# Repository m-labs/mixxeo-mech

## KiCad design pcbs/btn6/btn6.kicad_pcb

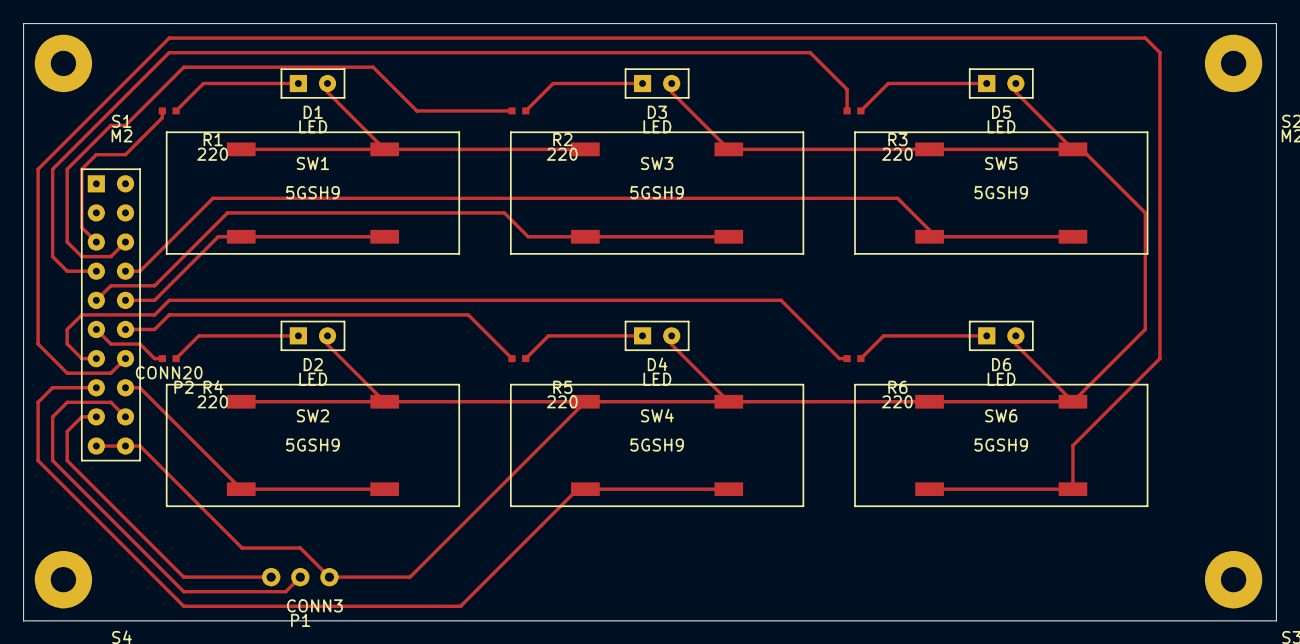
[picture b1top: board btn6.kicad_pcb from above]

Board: 2 copper layers, 109.2 x 52.1 mm, 24 parts (0 on the bottom side), 21 nets.

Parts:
D1, D2, D3, D4, D5, D6: LED; LED5x2
P1: CONN3
P2: CONN20
R1, R2, R3, R4, R5, R6: 220; 0402
S1, S2, S3, S4: M2
SW1, SW2, SW3, SW4, SW5, SW6: 5GSH9

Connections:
unnamed: P2.12, R5.1
unnamed: P2.13, R6.1
unnamed: P2.14, SW6.3, SW6.4
unnamed: P1.1, P2.17
unnamed: P1.2, P2.18
unnamed: P2.8, SW5.3, SW5.4
unnamed: P2.10, SW1.3, SW1.4
unnamed: D5.1, R3.2
unnamed: D3.1, R2.2
unnamed: P2.5, R1.1
unnamed: P2.16, SW2.3, SW2.4
unnamed: P2.15, SW4.3, SW4.4
unnamed: P2.9, SW3.3, SW3.4
unnamed: P2.6, R2.1
unnamed: P2.7, R3.1
unnamed: P2.11, R4.1
unnamed: D1.1, R1.2
unnamed: D6.1, R6.2
unnamed: D4.1, R5.2
unnamed: D2.1, R4.2
unnamed: D1.2, D2.2, D3.2, D4.2, D5.2, D6.2, P1.3, P2.19, P2.20, SW1.1, SW1.2, SW2.1, SW2.2, SW3.1, SW3.2, SW4.1, SW4.2, SW5.1, SW5.2, SW6.1, SW6.2

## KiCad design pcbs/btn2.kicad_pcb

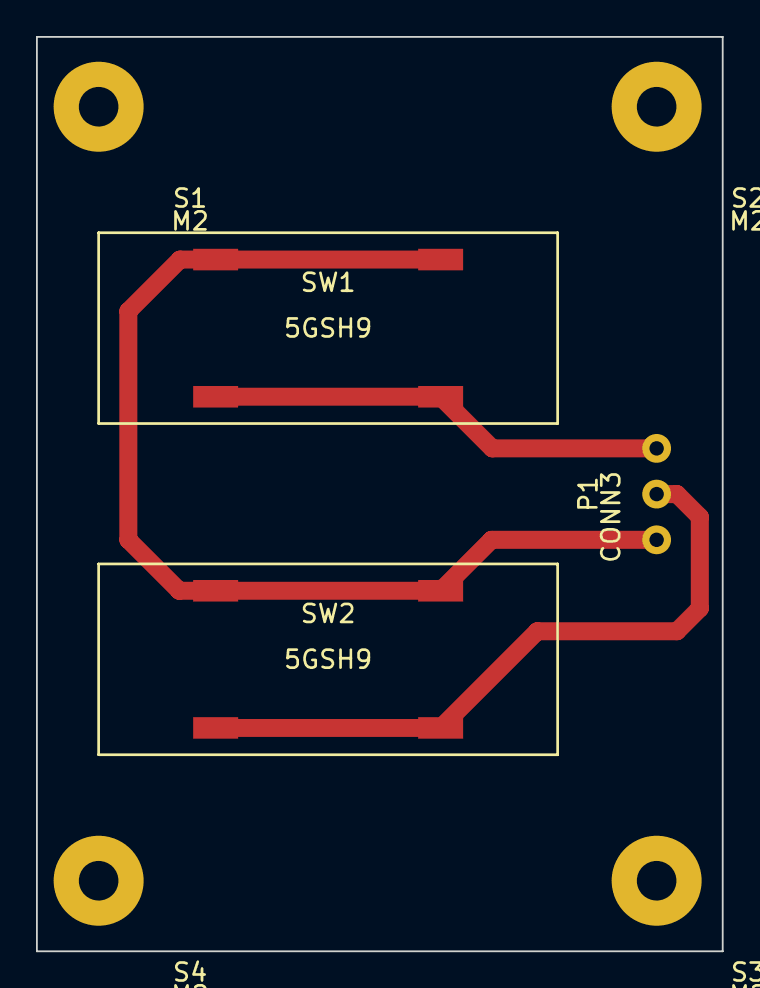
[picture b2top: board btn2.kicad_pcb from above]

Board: 2 copper layers, 38.1 x 50.8 mm, 7 parts (0 on the bottom side), 3 nets.

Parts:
P1: CONN3
S1, S2, S3, S4: M2
SW1, SW2: 5GSH9

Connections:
unnamed: P1.1, SW1.3, SW1.4
unnamed: P1.2, SW2.3, SW2.4
unnamed: P1.3, SW1.1, SW1.2, SW2.1, SW2.2

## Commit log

2014-04-23 Add top plate design
2014-04-23 Add parts list
2014-04-26 center pots
2014-04-29 New parts
2014-05-01 Add btn2 board
2014-05-01 pcbs: rename
2014-05-01 pcbs: use one folder per board
2014-05-01 top_plate: fix btn6 screw positions
2014-05-01 top_plate: recenter LEDs and fix QCad-induced coordinate fuckups
2014-05-01 Add BTN6 board
2014-05-01 top_plate: adapt to new pot/encoder
2014-05-01 pcbs: add Gerber folders
